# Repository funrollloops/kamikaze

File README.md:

## Build instructions

```bash
sudo apt install \
  cmake ninja-build git build-essential pkg-config qt4-default python3-pip \
  libavcodec-dev libavformat-dev libswscale-dev libavutil-dev libjpeg-dev
pip install conan
mkdir -p build/Release
(cd build/Release && conan install ../.. --build=missing)
cmake -B build/Release -DCMAKE_BUILD_TYPE=Release -GNinja \
  -DCMAKE_EXPORT_COMPILE_COMMANDS=ON -DCMAKE_CXX_CLANG_TIDY=/usr/bin/clang-tidy-14
ninja -C build/Release
```

Using a virtualenv, CC=clang-14, CXX=clang++-14 are recommended. conan should
use the same compiler for dependencies as the main build. direnv can be used to
automate loading the virtualenv and setting the compiler options.

## Run the Blaster controller
The main program is `kamikaze`; run with all features enabled:
```bash
ninja -C build kamikaze &&
build/kamikaze --logtostderr \
  --spi /dev/spidev0.0 \
  --save_directory=$(pwd)/output
```

`--spi` enables talking to the slave over SPI, which will only work on a
Raspberry Pi connected to the daughterboard with a flashed Atmega328p (see the
arduino/ folder). If using the prototype that communicates over USB Serial,
pass `--arduinoio_tty=/dev/ttyACM0` (or ACM1 etc) instead of `--spi`.

On a dev machine leave off both `--spi` and `--arduinoio_tty` to stub out all
daughterboard communication.

## CLI for controlling the hardware

Test the Arduino communication code with `robot_test`:
```bash
ninja -C build robot_test && build/robot_test
```

## The uploader binary

The uploader binary lives in `uploader/`. It monitors the `shots` directory, or
any directory that is passed to it, and uploads any files that it finds that
[meet the specification](https://github.com/audiodude/kamikaze/blob/master/uploader/file_collector.py#L11).
To run it, first install the requirements in uploader/requirements.txt:

`$ sudo pip install -r uploader/requirements.txt`

Next, obtain a copy of aws_credentials.secret, which contains the AWS
credentials in the boto3 format. This format is documented on
[the boto3 site](https://boto3.amazonaws.com/v1/documentation/api/latest/guide/configuration.html#shared-credentials-file)
Basically, if you have an `aws_access_key_id` and an `aws_secret_access_key`,
you can easily create this plain text file for yourself. Otherwise, you can
obtain credentials from a teammate.

Finally, run the binary  with an environment variable, like a normal python
script:

`AWS_SHARED_CREDENTIALS_FILE=aws_credentials.secret python uploader/uploader.py --watch_dir=/path/to/shots --upload_db=path/to/uploads.sqlite`

The `AWS_SHARED_CREDENTIALS_FILE` environment variable is consumed by the boto3
AWS integration library and used automatically to connect to S3, where the
files are uploaded to. Also note that by default the images are uploaded to the
`blaster-gallery` bucket in the `US West (N. California)` region.

The `--watch_dir` flag is the directory that will be monitored for images
in the specified format.

The `--upload_db` flag is the path to the sqlite database file that will be
used to track uploads. It's perfectly fine to pass the path to a file that does
not exist yet, and it will be created.

See also the repo that handles the display of these images (private):
[raygun](https://github.com/audiodude/raygun)

## Install services (optional)

Install the systemd service to auto-start the controller with
```bash
sudo systemctl enable $(pwd)/kamikaze-controller.service
./configure_autossh.sh  # Might need some configuration.
```

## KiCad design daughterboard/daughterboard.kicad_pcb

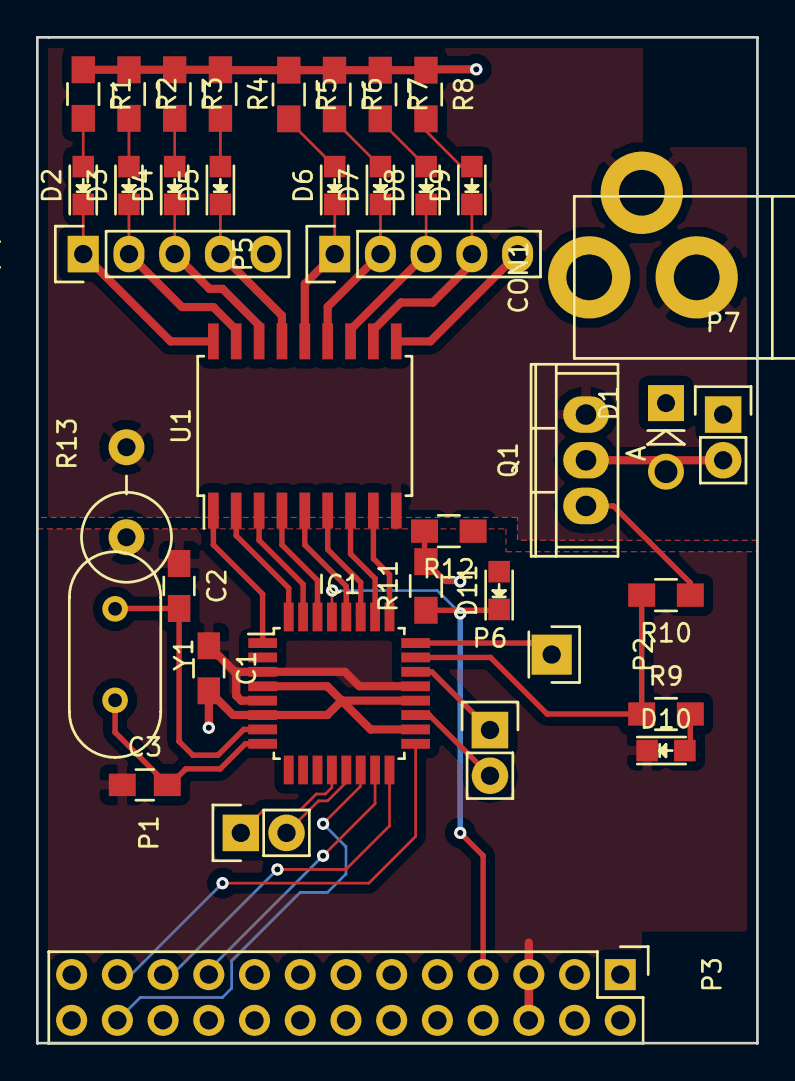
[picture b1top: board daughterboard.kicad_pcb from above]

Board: 2 copper layers, 40.0 x 55.9 mm, 39 parts (0 on the bottom side), 45 nets.

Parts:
C1: 100nF; C_0805_HandSoldering
C2, C3: 22pF; C_0805_HandSoldering
CON1: 12V_JACK; BARREL_JACK
D1: 1N4007; Diode_DO-41_SOD81_Vertical_AnodeUp
D2, D3, D4, D5, D6, D7, D8, D9: LED_0805
D10: YELLOW; LED_0805
D11: RED; LED_0805
IC1: ATMEGA328P-A; TQFP-32_7x7mm_Pitch0.8mm
P1: X_PB01; Pin_Header_Straight_1x02
P2: X_PC1; Pin_Header_Straight_1x01
P3: CONN_13X2; Pin_Header_Straight_2x13
P4: AZIMUTH; Pin_Header_Straight_1x05
P5: ELEVATION; Pin_Header_Straight_1x05
P6: X_ADC67; Pin_Header_Straight_1x02
P7: VALVE; Pin_Header_Straight_1x02
Q1: TIP120; TO-220
R1, R2, R3, R4, R5, R6, R7, R8: 500; R_0805_HandSoldering
R9, R12: 100; R_0805_HandSoldering
R10: 1K; R_0805_HandSoldering
R11: 10K; R_0805_HandSoldering
R13: SHORT; Resistor_Vertical_RM5mm
U1: ULN2803A; SOIC-18_7.5x11.6mm_Pitch1.27mm
Y1: 8MHz; HC-49V

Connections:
+3V3: C1.2, IC1.4, IC1.6, IC1.18, IC1.20, P3.1, R11.2, R12.2
+12V: CON1.1, D1.1, P4.5, P5.5, P7.1, R1.1, R2.1, R3.1, R4.1, R5.1, R6.1, R7.1, R8.1, U1.10
/GPIO4: D11.1, IC1.29, P3.7, R11.1
/GPIO8(CE0): IC1.14, P3.24
/GPIO9(MISO): IC1.16, P3.21
/GPIO10(MOSI): IC1.15, P3.19
/GPIO11(SCLK): IC1.17, P3.23
/S1: IC1.1, U1.1
/S2: IC1.32, U1.2
/S3: IC1.31, U1.3
/S4: IC1.30, U1.4
/S5: IC1.28, U1.5
/S6: IC1.27, U1.6
/S7: IC1.26, U1.7
/S8: IC1.25, U1.8
/VALVE: IC1.23, R9.1, R10.2
/XTAL1: C2.2, IC1.7, Y1.1
/XTAL2: C3.2, IC1.8, Y1.2
GND: CON1.2, CON1.3, Q1.3, R13.2, U1.9
GNDD: C1.1, C2.1, C3.1, D10.1, IC1.3, IC1.5, IC1.21, P3.5, P3.6, R13.1
unnamed: D1.2, P7.2, Q1.2
unnamed: D2.1, P4.1, U1.18
unnamed: D2.2, R1.2
unnamed: D3.1, P4.2, U1.17
unnamed: D3.2, R2.2
unnamed: D4.1, P4.3, U1.16
unnamed: D4.2, R3.2
unnamed: D5.1, P4.4, U1.15
unnamed: D5.2, R4.2
unnamed: D6.1, P5.1, U1.14
unnamed: D6.2, R5.2
unnamed: D7.1, P5.2, U1.13
unnamed: D7.2, R6.2
unnamed: D8.1, P5.3, U1.12
unnamed: D8.2, R7.2
unnamed: D9.1, P5.4, U1.11
unnamed: D9.2, R8.2
unnamed: D10.2, R9.2
unnamed: D11.2, R12.1
unnamed: IC1.12, P1.1
unnamed: IC1.13, P1.2
unnamed: IC1.19, P6.2
unnamed: IC1.22, P6.1
unnamed: IC1.24, P2.1
unnamed: Q1.1, R10.1

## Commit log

2017-09-26 Add flags to disable preview, skip waiting between images
2017-09-26 Add support for reading video from the webcam
2017-09-26 When preview is disabled, print debug info to stdout instead
2017-09-26 Read the latest state byte, not just the next one
2017-09-27 Clean up unused python scripts
2017-09-27 Clean up unused open mouth model
2017-10-15 Implement async firmware (Serial I/O, no error checking)
2017-10-15 Clean up CUDA code
2017-10-15 Switch p/P to t/m for tell/move
2017-10-15 Re-implement Robot to use new firmware
2017-10-15 Minimal change to get cc/main.cc compiling again
2017-10-15 Flush serial on ClearReadBuffer() and SendLine()
2017-10-15 Wait 1ms between tell() retries
2017-10-15 Reduce range of motion in robot_test.cc
2017-10-15 slightly increase cmd buffer len, zero length commands are ignored
2017-10-16 Increase max wait for a serial byte to 50ms
2017-10-16 Add a mutex to make sure only one command is being sent at a time
2017-10-16 Print response for SendAndRead() calls
2017-10-22 Change port to ttyUSB0
2017-10-22 Add files and examples for flashing/communicating with Arduino slave over SPI
2017-10-22 Add rpicam include directory
2017-10-23 Switch to SPI for pi->atmega comm
2017-10-23 Fix print of SPI mode
2017-10-30 Get firmware working on breadboard
2017-10-30 Remove Wire dependency
2017-10-30 Switch prescaler to 64 to fix small error in interrupt rate
2017-10-30 Switch to 8-bit timer2 for ticks
2017-10-30 Tighten up the SPI ISR
2017-10-30 Initial version of board design
2017-10-30 Generate netlist, choose footprints
2017-11-12 Layout parts (backwards)
2017-11-12 fix pin assignments
2017-11-12 fix board size to allow use of camera port, add keepouts for mounting holes
2017-11-12 Reassign pins around to simplify layout
2017-11-12 Route everything except optional headers
2017-11-12 add GND->GNDD short resistor, connect X_PB01 but not X_PD4567
2017-11-12 Fix DRC caused by stray track
2017-11-12 Slightly increase board size, extend ground/power planes up to edge cuts
2017-11-12 Tweak output parameters for Oshpark
2017-11-12 Add custom OSHPark-compatible barrel jack footprint
2017-11-12 Tweak footprint for barrel jack, move unused port off board / tweak trace
2017-12-03 update avrdude.conf to match pcb
2017-12-03 Add upload-spi command, enable compiler warnings
2017-12-03 Add custom command/target to run spi test
2017-12-03 Update stepper pins to match PCB
2017-12-24 Quick changes to use absolute positioning in recognition cycle
2017-12-24 Remove unused header from PCB
2017-12-24 Add interactive mode to robot_test, add to CMakeLists.txt
2017-12-24 Switch to AddExternalProject instead of add_subdirectory, add glog
2017-12-24 Switch to AddExternalProject and glog
2017-12-24 master/main.cc: clean up action code, fix bugs in it
2017-12-24 Fix build bugs
2017-12-24 Fix manual move orientation
2017-12-24 Swap std::cout/cerr for LOG
2017-12-24 Face tracking works end-to-end!
2017-12-24 Speed up vertical tracking
2018-01-06 Add more intermediate targets to build file
2018-01-06 CMakeLists: Add imported libraries to attach dependency information to
2018-01-06 Refactor slightly in preparation for saving images
2018-01-06 Set capture FPS to 60
2018-01-06 Factor out AsyncCaptureSource to allow for video capture
2018-01-06 Capture multiple images, save video (behind --save_video flag)
2018-01-06 Taking 1 photo works!
2018-01-06 Build OpenCV as an external project
2018-01-06 Use URL instead of saved OpenCV path, turn off UPDATE_COMMAND
2018-01-06 Fix writing video
2018-01-06 Add additional docs on running kamikaze command
2018-01-06 Simplify command to build/run kamikaze a bit
2018-01-23 Add .gitignore for shots directory
2018-01-23 First iteration of uploader code. For now, all it does is monitor the shots directory and log paths that would have been uploaded.
2018-01-23 Uploader requirements.txt
2018-01-23 Update README with basic info on prototype uploader
2018-01-27 Multiprocessing version of uploader, with sqlite3 db for persisting workload.
    Still doesn't actually upload anything.
2018-01-29 Add secrets to gitignore
2018-01-29 Working prototype of the uploader that actually uploads to S3 and marks work as completed.
    Still not handling package IDs correctly, in that they are all currently hardcoded to 'foobar'.
2018-01-29 Add boto3 to requirements.txt
2018-04-30 Add systemd unit file
2018-04-30 Make preview window resizable
2018-04-30 Instructions on installing systemd service
2018-04-30 Add instructions to build and run
2018-05-01 Install to install dir, not binary dir
2018-05-03 Make uploader.py executable
2018-05-03 Update picture filenames to match uploader
2018-05-03 py: Remove warpAffine call
2018-05-03 Fix top-level kamikaze and robot_test targets
2018-05-03 Clean up target aliases
2018-05-06 Add reverse-ssh-proxy sevice
2018-05-07 Use DNS instead of hardcoded IP
2018-06-11 Fix bugs in build, instructions
2018-06-17 Add --track flag to disable/enable face tracking
2018-06-17 Calibration for SF blaster
2018-06-17 Add documentatio to robot_test
2018-06-18 Add autossh configuration script
2018-06-23 Ignore faces that are too large
2018-07-09 Add hello world grpc examples
2018-07-09 Add robot_proxy_server and robot_proxy_wrapper, wire into RobotFromFlags
2018-07-09 Add build to .gitignore
2018-07-10 Build fixes
2018-07-11 Fix CMake warnings
2018-07-14 Restore support for ArduinoIO (old bot)
2018-07-14 Calibration, seek while on target, bigger/smaller step keys
2018-07-15 Show both image-to-act and act-to-act latency
2018-07-15 Add flag to disable behavior to keep tracking while maybe_fire>0
2018-07-15 Add support for arrow keys in addition to WASD
2018-07-15 Hack up L/R moves for cc+arduinoio
2018-07-15 py: continue to seek when on target
2018-07-15 Fix video capture
2018-07-15 Add --webcam_skew_angle
2018-07-15 Move most useful constants to top of file
2018-07-15 Organize flags
2018-07-15 Reduce target size by half
2018-07-15 Upgrade to 3.4.2 + build face module
2018-07-15 Experiments with face recognizer
2018-07-15 Add detect time
2018-07-15 Add support for --tunnel_vision
2018-07-15 Cut waitKey time down to 1ms
2018-07-15 Add keys to print help, toggle preview/tracking
2018-07-15 Refactor main a bit
2018-07-22 Commit changes from DNA: auto-disable firing between shots
2018-07-22 Upgrade to OpenCV 3.4.2
2018-07-22 Move cc/ up to root
2018-07-22 Turn off unneeded OpenCV features, link OpenCV statically
2018-07-22 Fix bugs in controller build
2018-07-22 Split capture mutex into two for the latest image and video writer
2018-07-22 Bump up min face size a smidge
2018-07-22 statically link raspicam
2018-07-22 Propagate build type to controller subproject
2018-07-22 Rename arduino => firmware and daughterboard => pcb
2018-07-22 Make path to face haarcascade a flag, make it work from project root
2018-07-22 make raspicam dependency optional, default to OFF
2018-08-09 Tweak CFLAGS a bit
2018-08-12 Add Makefile as an alternative build method
2018-08-12 Split device flag for AVRDUDE and GCC
2018-08-12 Make avrdude.conf additive, not a replacement
2018-08-12 Remove cmake build for firmware, update README
2018-10-24 Update documentation for uploader
2018-10-25 Update more info in README
2018-10-25 Update README with correct S3 region
2022-05-29 Switch to Conan for dependency management
2022-05-29 Switch to #pragma once
2022-05-29 Fix clang-tidy warnings
